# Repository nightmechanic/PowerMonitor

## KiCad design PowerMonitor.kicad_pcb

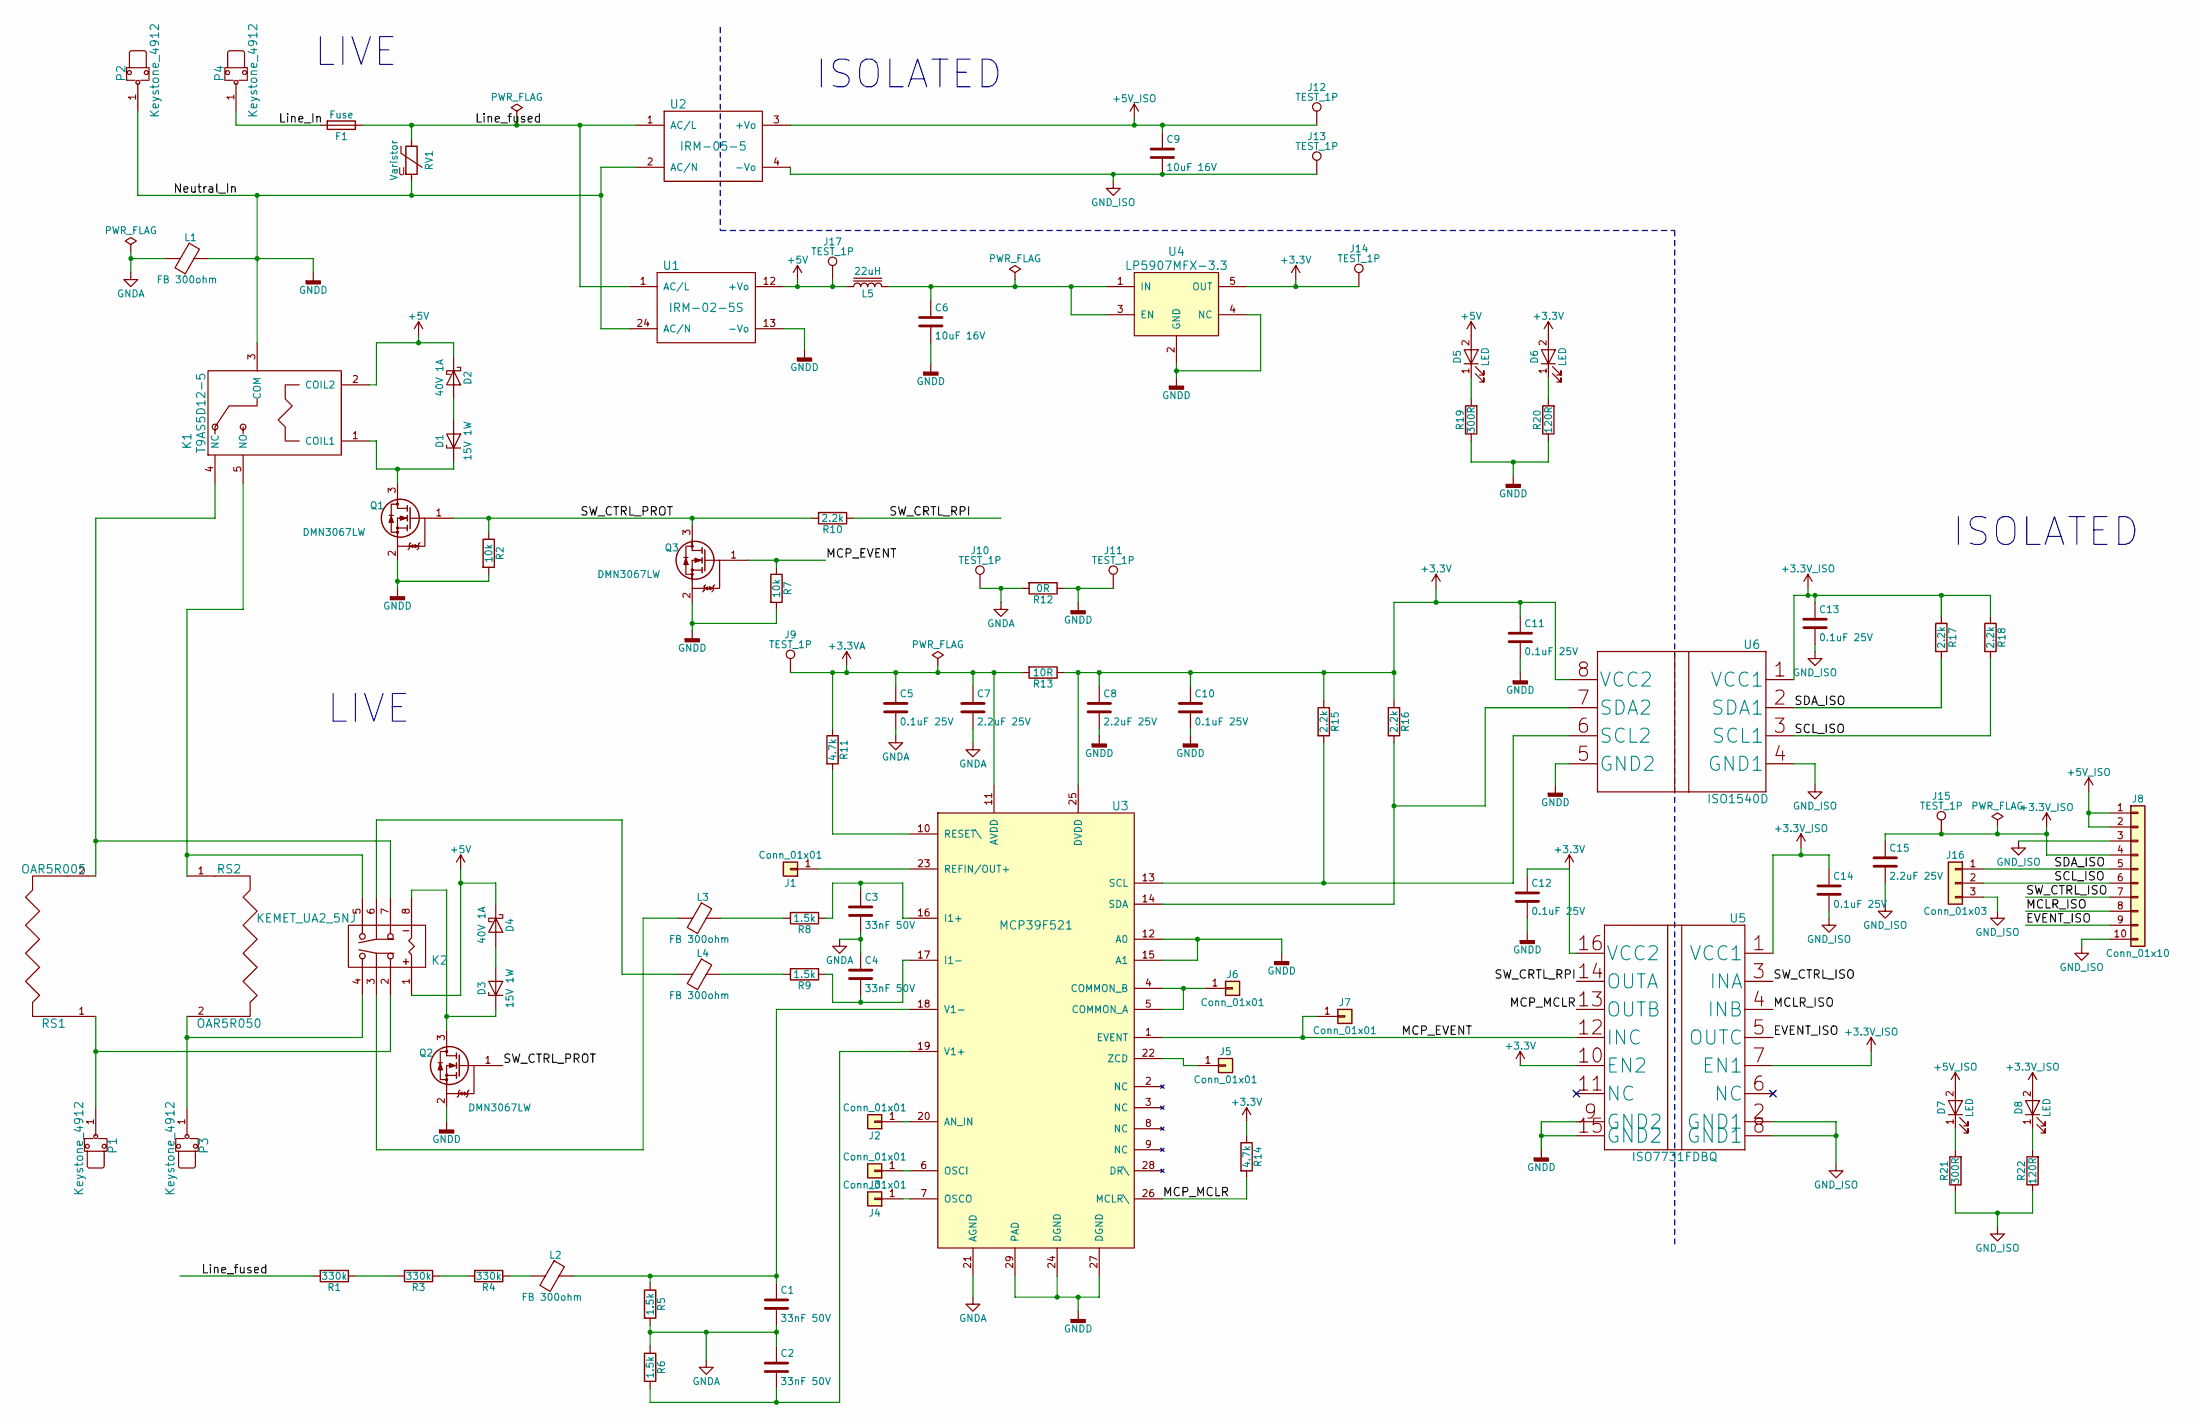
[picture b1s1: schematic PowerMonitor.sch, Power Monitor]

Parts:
C1, C2, C3, C4: 33nF 50V; C_0805
C5, C10, C11, C12, C13, C14: 0.1uF 25V; C_0603
C6, C9: 10uF 16V; C_1210
C7, C8, C15: 2.2uF 25V; C_0805
D1, D3: 15V 1W; DO-219AB
D2, D4: 40V 1A; DO-219AB
D5, D6, D7, D8: LED; LED_D3.0mm
F1: Fuse; Bel_MRT_Fuse
J1, J2, J3, J4, J5, J6, J7: Conn_01x01; Measurement_Point_Square-TH_Small
J8: Conn_01x10; Pin_Header_Straight_1x10_Pitch2.54mm
J9, J10, J11, J12, J13, J14, J15, J17: TEST_1P; Keystone_50XX_TP
J16: Conn_01x03; Pin_Header_Straight_1x03_Pitch2.54mm
K1: T9AS5D12-5; TE_T9AS_code1
K2: KEMET_UA2_5NJ; Kemet_UA2
L1, L2, L3, L4: FB 300ohm; C_0805
L5: 22uH; Murata_8200
P1, P2, P3, P4: Keystone_4912
Q1, Q2, Q3: DMN3067LW; SOT-323_SC-70
R1, R3, R4: 330k; R_1206
R2, R7: 10k; R_0603
R5, R6, R8, R9: 1.5k; R_0805
R10, R15, R16, R17, R18: 2.2k; R_0603
R11, R14: 4.7k; R_0603
R12: 0R; R_0603
R13: 10R; R_0805
R19, R21: 300R; R_0805
R20, R22: 120R; R_0805
RS1: OAR5R005; TE_OAR5
RS2: OAR5R050; TE_OAR5
RV1: Varistor; Bourns_MOV_14D431K
U1: IRM-02-5S; IRM-02-xS
U2: IRM-05-5; IRM-05-x
U3: MCP39F521; QFN-28-1EP_5x5mm_Pitch0.5mm_mod
U4: LP5907MFX-3.3; TI_DBV005
U5: ISO7731FDBQ; TI_DBQ0016A
U6: ISO1540D; TI_ISO1540D8

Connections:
+3.3VA: C5.1, C7.1, J9.1, R11.1, R13.2, U3.11 (AVDD)
+3.3V_ISO: C13.1, C14.1, C15.1, D8.2 (A), J8.4, J15.1, R17.1, R18.1, U5.1 (VCC1), U5.7 (EN1), U6.1 (VCC1)
+3V3: C8.1, C10.1, C11.1, C12.1, D6.2 (A), J14.1, R13.1, R14.1, R15.1, R16.1, U3.25 (DVDD), U4.5 (OUT), U5.10 (EN2), U5.16 (VCC2), U6.8 (VCC2)
+5V: D2.1 (K), D4.1 (K), D5.2 (A), J17.1, K1.2 (COIL2), K2.1, L5.1, U1.12 (+Vo)
+5V_ISO: C9.1, D7.2 (A), J8.1, J8.2, J12.1, U2.3 (+Vo)
/EVENT_ISO: J8.9, U5.5 (OUTC)
/Line_In: F1.2, P4.1
/Line_fused: F1.1, R1.2, RV1.1, U1.1 (AC/L), U2.1 (AC/L)
/MCLR_ISO: J8.8, U5.4 (INB)
/MCP_EVENT: J7.1, Q3.1 (G), R7.1, U3.1 (EVENT), U5.12 (INC)
/MCP_MCLR: R14.2, U3.26 (MCLR\), U5.13 (OUTB)
/SCL_ISO: J8.6, J16.2, R18.2, U6.3 (SCL1)
/SDA_ISO: J8.5, J16.1, R17.2, U6.2 (SDA1)
/SW_CRTL_RPI: R10.1, U5.14 (OUTA)
/SW_CTRL_ISO: J8.7, U5.3 (INA)
/SW_CTRL_PROT: Q1.1 (G), Q2.1 (G), Q3.3 (D), R2.1, R10.2
GND: C9.2, C13.2, C14.2, C15.2, J8.3, J8.10, J13.1, J16.3, R21.1, R22.1, U2.4 (-Vo), U5.2 (GND1), U5.8 (GND1), U6.4 (GND1)
GNDA: C1.2, C2.1, C3.2, C4.1, C5.2, C7.2, J10.1, L1.2, R5.2, R6.1, R12.2, U3.21 (AGND)
GNDD: C6.2, C8.2, C10.2, C11.2, C12.2, J11.1, K1.3 (COM), L1.1, P2.1, Q1.2 (S), Q2.2 (S), Q3.2 (S), R2.2, R7.2, R12.1, R19.1, R20.1, RV1.2, U1.13 (-Vo), U1.24 (AC/N), U2.2 (AC/N), U3.12 (A0), U3.15 (A1), U3.24 (DGND), U3.27 (DGND), U3.29 (PAD), U4.2 (GND), U4.4 (NC), U5.9 (GND2), U5.15 (GND2), U6.5 (GND2)
unnamed: C1.1, L2.1, R5.1, U3.18 (V1-)
unnamed: C2.2, R6.2, U3.19 (V1+)
unnamed: C3.1, R8.1, U3.16 (I1+)
unnamed: C4.2, R9.1, U3.17 (I1-)
unnamed: C6.1, L5.2, U4.1 (IN), U4.3 (EN)
unnamed: D1.1 (K), K1.1 (COIL1), Q1.3 (D)
unnamed: D1.2 (A), D2.2 (A)
unnamed: D3.1 (K), K2.8, Q2.3 (D)
unnamed: D3.2 (A), D4.2 (A)
unnamed: D5.1 (K), R19.2
unnamed: D6.1 (K), R20.2
unnamed: D7.1 (K), R21.2
unnamed: D8.1 (K), R22.2
unnamed: J1.1, U3.23 (REFIN/OUT+)
unnamed: J2.1, U3.20 (AN_IN)
unnamed: J3.1, U3.6 (OSCI)
unnamed: J4.1, U3.7 (OSCO)
unnamed: J5.1, U3.22 (ZCD)
unnamed: J6.1, U3.4 (COMMON_B), U3.5 (COMMON_A)
unnamed: K1.4 (NC), K2.7, RS1.2
unnamed: K1.5 (NO), K2.5, RS2.1
unnamed: K2.2, P1.1, RS1.1
unnamed: K2.3, L3.2
unnamed: K2.4, P3.1, RS2.2
unnamed: K2.6, L4.2
unnamed: L2.2, R4.1
unnamed: L3.1, R8.2
unnamed: L4.1, R9.2
unnamed: R1.1, R3.2
unnamed: R3.1, R4.2
unnamed: R11.2, U3.10 (RESET\)
unnamed: R15.2, U3.13 (SCL), U6.6 (SCL2)
unnamed: R16.2, U3.14 (SDA), U6.7 (SDA2)

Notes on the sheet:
ISOLATED
LIVE
LIVE

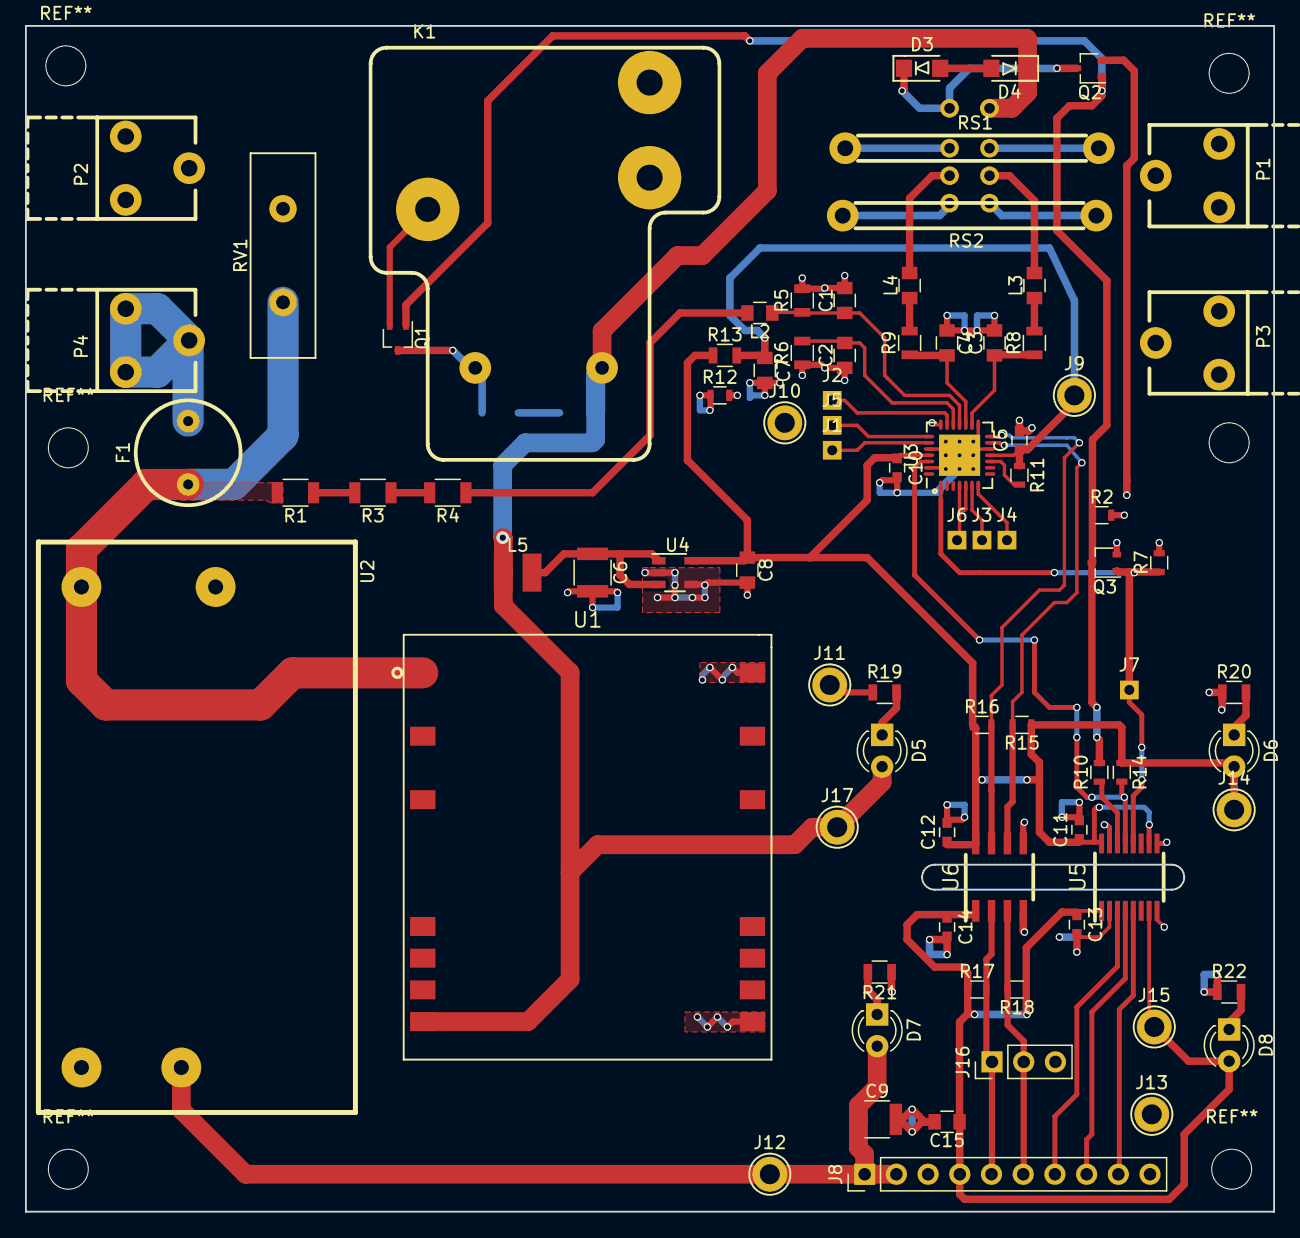
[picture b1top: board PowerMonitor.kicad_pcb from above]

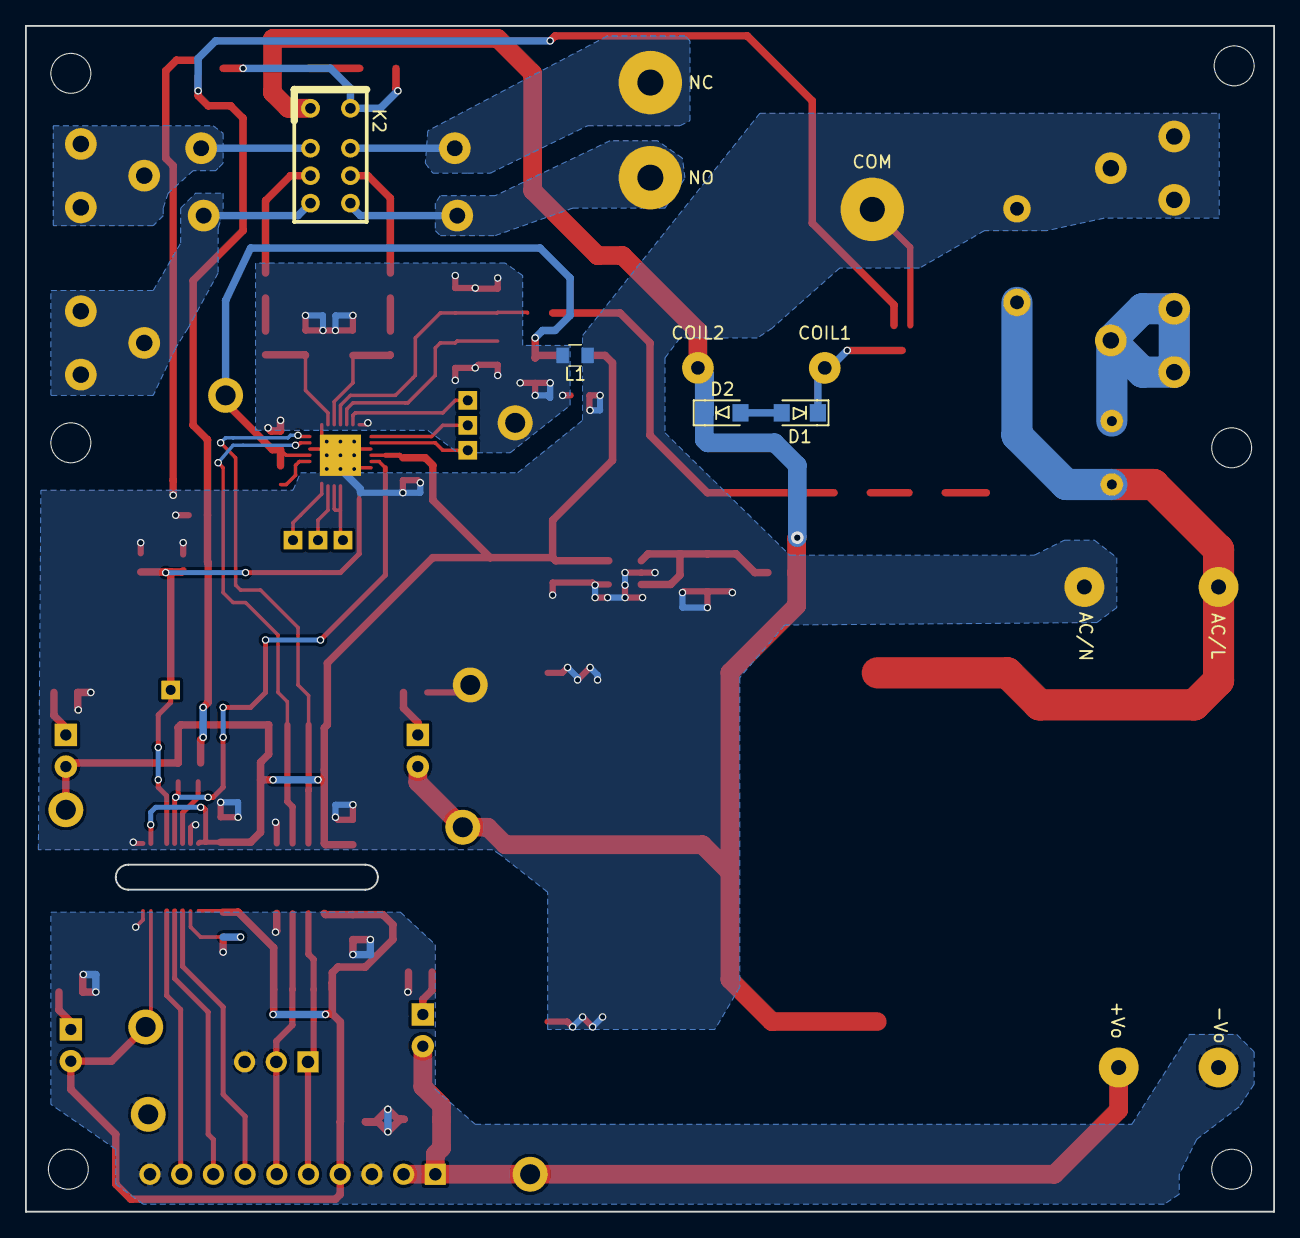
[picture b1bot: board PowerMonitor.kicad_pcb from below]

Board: 2 copper layers, 100.0 x 95.0 mm, 86 parts (4 on the bottom side), 52 nets.

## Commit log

2018-04-10 :lollipop: Added .gitattributes & .gitignore files
2018-04-10 starting
2018-05-01 schematic done
2018-05-01 another gnd_iso on connector
2018-05-03 added Live/isolated text
2018-05-03 initial placement
2018-05-13 placwmwnt v0.2
2018-05-17 layout started
2018-06-03 clean PCB DRC
